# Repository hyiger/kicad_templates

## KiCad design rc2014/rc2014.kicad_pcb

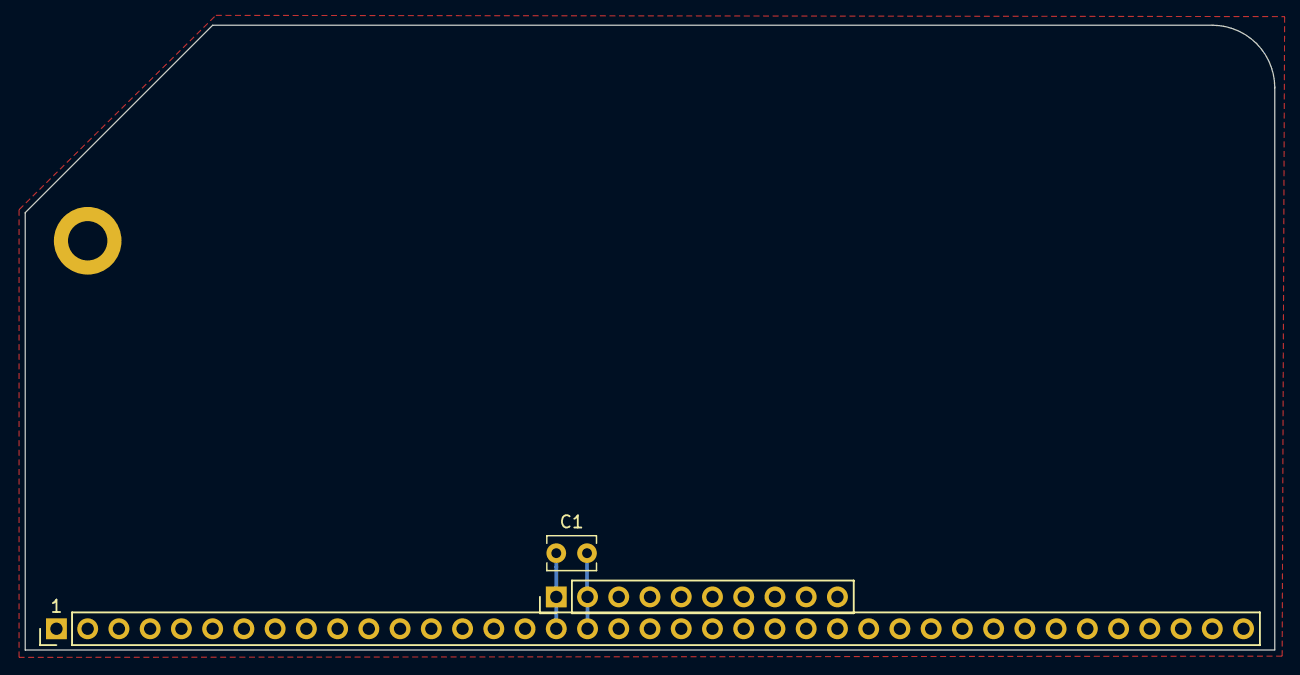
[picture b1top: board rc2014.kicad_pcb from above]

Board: 2 copper layers, 101.6 x 50.8 mm, 4 parts (0 on the bottom side), 2 nets.

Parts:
C1: 100nF; C_Disc_D3.8mm_W2.6mm_P2.50mm
J1: Z80 Bus; PinHeader_1x39_P2.54mm_Vertical
J2: Pro Bus; PinHeader_1x10_P2.54mm_Vertical
J4: M3 Mounting Hole; MountingHole_3.2mm_M3_ISO14580_Pad

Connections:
5V: C1.2, J1.18, J2.2
GND: C1.1, J1.17, J2.1, J4.1

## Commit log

2019-05-09 RC2014 blank template
